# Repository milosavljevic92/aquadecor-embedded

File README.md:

# 🐟 AquaLED Controller Firmware

Firmware for a PIC18F microcontroller written in **PicBASIC Pro**, designed to simulate natural day/night lighting cycles for aquariums and living spaces using PWM-controlled LED strips.

---

## 📦 Versions

This project has gone through three hardware and firmware revisions, each improving on the previous design.

| Version | Firmware | PCB Tool | Notes |
|---|---|---|---|
| v1.0 | Initial release | Spring Layout 6.0 | First prototype, basic day/night cycle |
| v2.0 | Extended relay scheduling | Spring Layout 6.0 | Added dual relay timers, improved menu |
| v3.0 | Current (`FW:3.0`) | Eagle PCB | Full feature set, temperature protection, maintenance mode |

PCB design files are included in the `/pcb` folder. Versions 1 and 2 were designed in **Spring Layout 6.0** (`.spl` files), while version 3 was redesigned from scratch in **Eagle PCB** (`.sch` / `.brd` files).

---

## ✨ Features

- **Automatic sunrise/sunset simulation** — gradually fades LED strips up and down over a configurable time window, mimicking natural daylight
- **4 independent PWM channels** — separate control for aquarium (3 channels) and room lighting (1 channel)
- **Manual brightness control** — override automatic mode and set each channel to a fixed brightness
- **2 internal relay timers** — schedule relay on/off times for pumps, heaters, or other devices
- **Temperature protection** — reads ambient temperature via LM75 sensor and shuts off LEDs if overheating is detected
- **Work/maintenance mode** — dedicated mode that slowly dims lights to a set working brightness and restores them when done
- **RTC timekeeping** — DS1307 real-time clock keeps accurate time even after power loss
- **Settings stored in EEPROM** — all schedules and preferences survive power cycles
- **LCD menu interface** — full 2-line LCD menu system with 6 tactile buttons for navigation

---

## 🔧 Hardware

| Component | Purpose |
|---|---|
| PIC18F microcontroller | Main CPU |
| DS1307 (I2C) | Real-time clock |
| LM75 (I2C) | Temperature sensor |
| 4x PWM outputs | LED strip control (10-bit PWM) |
| 2x Relay outputs | Pump / heater control |
| 2x16 LCD | Display and menu |
| 6 tactile buttons | Navigation (up, down, left, right, OK, maintenance) |
| EEPROM | Persistent settings storage |

---

## 🌅 How the Day/Night Cycle Works

Each of the 4 LED channels has independently configurable:

- **Sunrise** — start time, end time, start brightness → end brightness (fade up)
- **Sunset** — start time, end time, start brightness → end brightness (fade down)

The controller calculates the exact brightness every minute based on the elapsed time between the two endpoints, creating a smooth linear transition. You can configure different schedules for each channel — for example, channel 1 could peak earlier in the day than channel 3 to simulate shifting sun angles.

---

## 📋 Menu Structure

```
Main Menu
├── LED Light
│   ├── Automatic
│   │   ├── Aquarium Light
│   │   │   ├── Channel #1 → Sunrise / Sunset config
│   │   │   ├── Channel #2 → Sunrise / Sunset config
│   │   │   └── Channel #3 → Sunrise / Sunset config
│   │   └── Room Light    → Sunrise / Sunset config
│   └── Manual
│       ├── Aquarium Light → Set channels 1-3 manually
│       └── Room Light     → Set channel 4 manually
├── Internal Switches
│   ├── Switch #1 → ON time / OFF time
│   └── Switch #2 → ON time / OFF time
└── Tools
    ├── Set Time
    └── Restore Defaults
```

---

## 🔑 Button Reference

| Button | Action |
|---|---|
| UP / DOWN | Increase or decrease value |
| LEFT | Go back / exit menu |
| RIGHT | Move to next field |
| OK | Confirm / enter submenu |
| MAINTENANCE | Toggle maintenance (work light) mode |

---

## 🛠️ Building & Flashing

1. Open the `.pbp` source file in **PicBASIC Pro** compiler
2. Target: **PIC18F** (configured for internal 16MHz oscillator)
3. Compile and flash using your preferred PIC programmer (e.g. PICkit, ICD)
4. On first boot the firmware auto-initializes EEPROM with default schedules

> First boot is detected automatically — no manual EEPROM erase needed.

---

## ⚡ Hardware Specifications

| Parameter | Value |
|---|---|
| Supply voltage | 12V DC |
| Output channels | 4 independent channels |
| Output current | 2.5A per channel |
| Max output power | 120W total |
| Real-time clock | Yes (battery-backed) |
| Overheating protection | Yes (automatic LED shutoff) |
| Power consumption | Low (PIC18F sleep-capable architecture) |

---

## ⚙️ Configuration

All settings are adjusted through the LCD menu and saved to EEPROM automatically. There is no need to recompile or reflash to change schedules or brightness levels.

To restore factory defaults, navigate to **Tools → Default Settings → YES**.

---

## 📄 License

MIT — free to use, modify, and distribute.

---

*Built by [Tecomatic](https://tecomatic.rs)*

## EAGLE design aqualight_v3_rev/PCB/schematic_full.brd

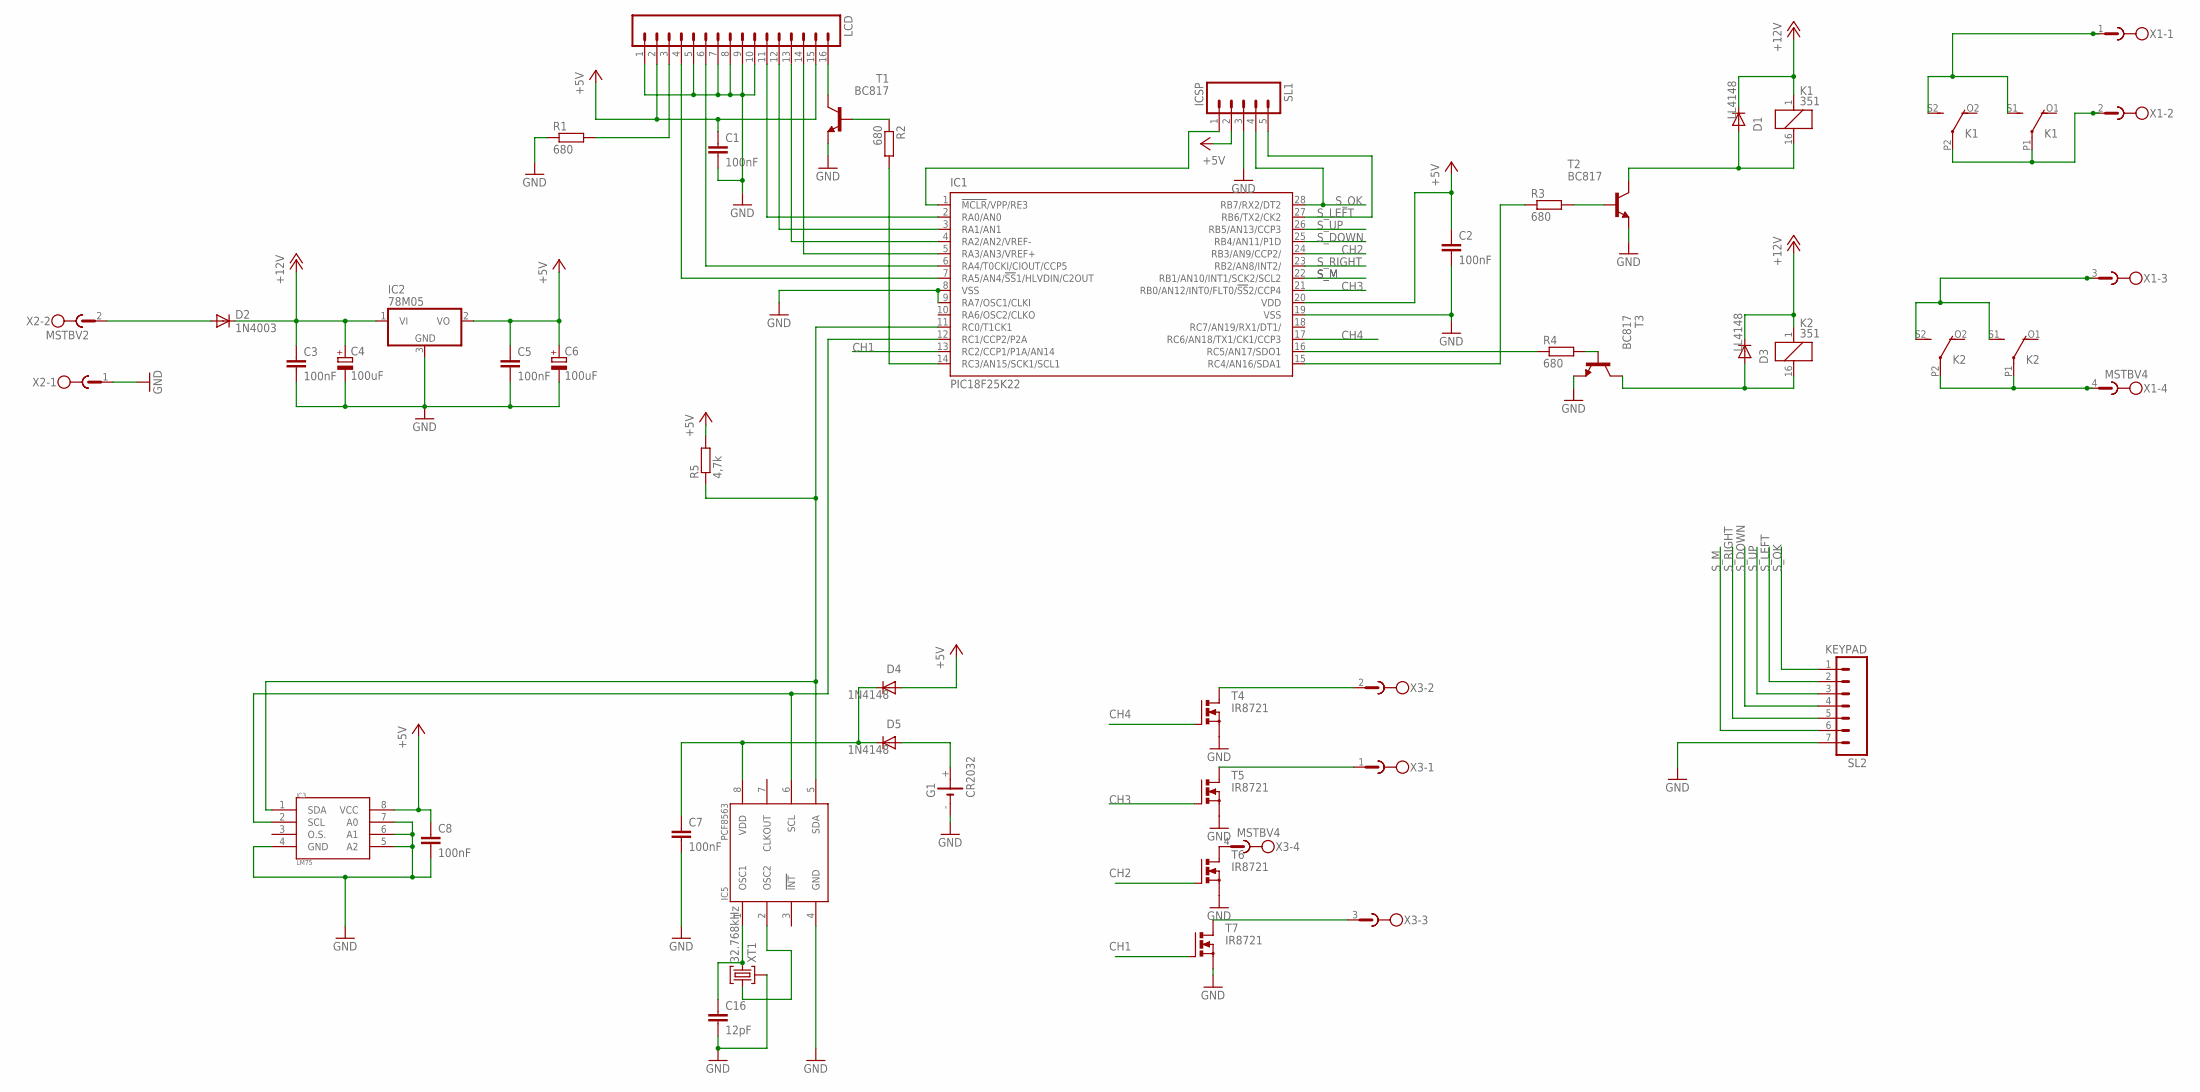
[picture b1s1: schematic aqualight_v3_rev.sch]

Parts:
C1, C2, C3, C5, C7, C8: 100nF; C0805K
C4: 100uF; E2,5-6E
C6: 100uF; E2,5-6
C16: 12pF; C0805K
D1, D3: LL4148; DO214BA
D2: 1N4003; DO41-10
D4, D5: 1N4148; DO214BA
G1: CR2032
IC1: PIC18F25K22; SSOP28
IC2: 78M05; TO252
IC3: LM75; SO08
IC5: PCF8563; SO08
K1, K2: 351
LCD: M16; 16P
R1, R2, R3, R4: 680; M0805
R5: 4,7k; M0805
SL1: ICSP; 05P
SL2: KEYPAD; 07PA
T1, T2, T3: BC817; SOT23-BEC
T4, T5, T6, T7: IR8721; TO252
X1, X3: MSTBV4
X2: MSTBV2
XT1: 32.768kHz; XTMINI

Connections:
+5V: C1.1, C2.1, C5.1, C6.+, C8.1, D4.A, IC1.20 (VDD), IC2.2 (VO), IC3.8 (VCC), LCD.2, LCD.15, R5.2, SL1.2
+12V: C3.1, C4.+, D1.C, D2.C, D3.C, IC2.1 (VI), K1.1, K2.1
CH1: IC1.13 (RC2/CCP1/P1A/AN14), T7.1 (G)
CH2: IC1.24 (RB3/AN9/CCP2/), T6.1 (G)
CH3: IC1.21 (RB0/AN12/INT0/FLT0/!SS!2/CCP4), T5.1 (G)
CH4: IC1.17 (RC6/AN18/TX1/CK1/CCP3), T4.1 (G)
GND: C1.2, C2.2, C3.2, C4.-, C5.2, C6.-, C7.2, C8.2, C16.2, G1.-, IC1.8 (VSS), IC1.9 (RA7/OSC1/CLKI), IC1.19 (VSS), IC2.3 (GND), IC3.4 (GND), IC3.5 (A2), IC3.6 (A1), IC3.7 (A0), IC5.4 (GND), LCD.1, LCD.5, LCD.7, LCD.8, LCD.9, LCD.10, R1.1, SL1.3, SL2.7, T1.E, T2.E, T3.E, T4.3 (S), T5.3 (S), T6.3 (S), T7.3 (S), X2.1, XT1.P$3 (3)
unnamed: D5.A, G1.+
unnamed: K1.S1 (S), K1.S2 (S), X1.1
unnamed: K2.P1, K2.P2, X1.4
unnamed: T5.2 (D), X3.1
unnamed: D2.A, X2.2
unnamed: IC1.15 (RC4/AN16/SDA1), R3.1
unnamed: T4.2 (D), X3.2
unnamed: IC5.2 (OSC2), XT1.P$1 (1)
unnamed: T6.2 (D), X3.4
unnamed: IC1.11 (RC0/T1CK1), IC3.1 (SDA), IC5.5 (SDA), R5.1
unnamed: IC1.12 (RC1/CCP2/P2A), IC3.2 (SCL), IC5.6 (SCL)
unnamed: C7.1, D4.C, D5.C, IC5.8 (VDD)
unnamed: IC1.2 (RA0/AN0), LCD.11
unnamed: IC1.3 (RA1/AN1), LCD.12
unnamed: IC1.4 (RA2/AN2/VREF-), LCD.13
unnamed: IC1.5 (RA3/AN3/VREF+), LCD.14
unnamed: IC1.6 (RA4/T0CKI/CIOUT/CCP5), LCD.6
unnamed: T7.2 (D), X3.3
unnamed: IC1.7 (RA5/AN4/!SS!1/HLVDIN/C2OUT), LCD.4
unnamed: LCD.3, R1.2
unnamed: D1.A, K1.16 (2), T2.C
unnamed: C16.1, IC5.1 (OSC1), XT1.P$2 (2)
unnamed: D3.A, K2.16 (2), T3.C
unnamed: LCD.16, T1.C
unnamed: R4.2, T3.B
unnamed: R3.2, T2.B
unnamed: K1.P1, K1.P2, X1.2
unnamed: IC1.16 (RC5/AN17/SDO1), R4.1
unnamed: R2.1, T1.B
unnamed: IC1.14 (RC3/AN15/SCK1/SCL1), R2.2
unnamed: IC1.1 (!MCLR!/VPP/RE3), SL1.1
SWITCH2_IN: K2.S1 (S), K2.S2 (S), X1.3
S_DOWN: IC1.25 (RB4/AN11/P1D), SL2.4
S_LEFT: IC1.27 (RB6/TX2/CK2), SL1.5, SL2.2
S_M: IC1.22 (RB1/AN10/INT1/SCK2/SCL2), SL2.6
S_OK: IC1.28 (RB7/RX2/DT2), SL1.4, SL2.1
S_RIGHT: IC1.23 (RB2/AN8/INT2/), SL2.5
S_UP: IC1.26 (RB5/AN13/CCP3), SL2.3

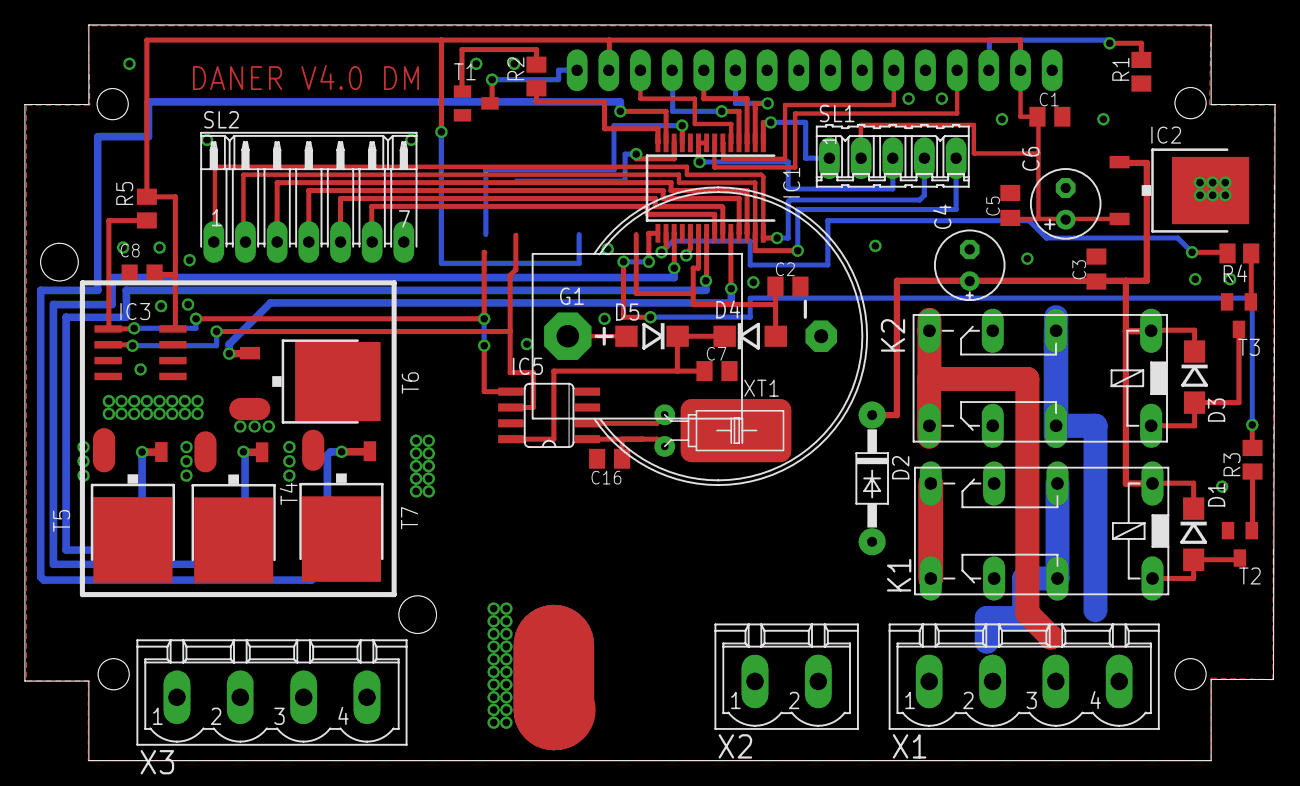
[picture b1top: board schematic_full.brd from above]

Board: 2 copper layers, 100.3 x 59.0 mm, 40 parts (1 on the bottom side), 45 nets.

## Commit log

2026-06-04 renemae
2026-06-04 renename staff
2026-06-04 remove some files
2026-06-04 add licence
2026-06-04 add readme
